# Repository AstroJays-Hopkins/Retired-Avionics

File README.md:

# Onboard Avionics and Ground Support Electronics

Avionics computer programs (excluding ground station GUI) and circuit schematics.  Program design documents and other non-program files may be found on team internet storage.

## Some directories of interest

* ```propulsion/```  --- Programs that control rocket propulsion systems
  * ```propulsion/darts```  --- Rocket's Data Acquisition, Recording, and Telemetry System
  * ```propulsion/ignition```  --- Programs to monitor and actuate the rocket's ignition hardware
* ```recovery/```  --- Programs that make sure the rocket can fly again
* ```ground-tests/```  --- Programs to help determine if the rocket can (should) even fly in the first place
* ```libraries/```  --- Custom libraries written in-house (one-of-a-kind --- you won't find them elsewhere!) and modified sensor libraries.

For detailed information about a particular subsystem, please consult the READMEs in that subsystem's directory.

_Made in Baltimore with love, tears, caffine, swearing, all-nighters, hair-pulling, stolen code, grimacing, git-cursing, and shocking realizations about engineering._

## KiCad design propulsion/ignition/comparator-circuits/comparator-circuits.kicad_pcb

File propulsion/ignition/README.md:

# Ignition system programs and schematics

Name says it all.

Schematic and PCB design are done using [KiCAD](http://kicad-pcb.org/).

## Files

* ```schematic/```  --- Schematics for ignition system
* ```comparator-circuits/```  --- Schematics and PCB design files for the
  continuity tester circuits used in the ignition system

### Things to know about the schematics

* Suggested changes to the schematics are presented in the ```future``` branch.

## Explanation of system

> _Bug avnoks for further details._

The ignition system consists of three parts: the part to light the ematch,
the part to open the oxidizer ball valve,
and the radio device (the "football") that controls the first two parts.
The system is designed around the following principles:

* Safety is implemented in hardware.
  The system's safety should arise from its physical properties,
  not from software checks.
  > Use physical switches as opposed to if statements.
  Never should software be the only thing preventing an unauthorised launch.
* The system should fail safe.
  Should a component of the system stop working,
  it should do so in a way that does not compromise the rest of the system
  and does not cause an unauthorised launch.
* Ultimate control of the system and the launch of the rocket
  should reside in one person.
  This is accomplished by giving the one key
  that arms all switches throughout the system and launches the rocket
  to only one person who is also the last person to leave the pad.
* The system should communicate unambiguously.

### Ematch

The ematch part of the system consists of a battery,
an ematch,
and circuitry to prevent the battery from lighting the ematch
when it's not supposed to.
The battery is housed alongside a relay, radio, and other circuitry
in a relay box located 50 imperial feet away from the rocket
(the radio recieves the command to light the ematch
and activates the relay to connect the battery
to the wires going to the ematch).
The ematch is buried in a block of propellant
suspended in the fuel grain of the rocket;
it is connected to the relay box
through a long wire and some more safety circuitry.
The safety circuitry consists primarily of voltage warning signals,
two switches,
and continuity testers

#### Voltage warning signals

A buzzer and a white LED
in the relay box
and another buzzer and white LED in the rocket
warn launch personnel when there is voltage across the wire
that supplies the ematch with electricity.
Should launch personnel observe these buzzers and LEDs activate,
they should immediately retreat from the pad
and await further instructions.

**FIXME:** Identify frequency of buzzer.

#### Switches

Two key switches are built into the circuit:
a shunt switch,
which is on the relay box,
and a safety switch,
which is on the rocket.
The shunt switch shorts out the wires
that supply electricity to the ematch.
It should be closed whenever personnel are closer to the rocket
than the relay box is (within 50 feet of the rocket).
The safety switch interrupts the wires supplying electricity to the ematch.
It should remain open unless personnel
are about to retreat to a safe area for launch.
Personnel should never close the safety switch
if they observe the voltage warning signals described above.

#### Continuity testers

The continuity testers detect when the switches,
relay,
and ematch in the system have continuity.
For the relay and switches,
the testers sound a buzzer and light an LED
when the component monitored is in an unsafe state
(unsafe means that fewer things need to happen
in order for the rocket to launch).

The continuity testers are built from comparators.
The theory behind them can be found at David Johnson-Davies's
[post on a similar tester.](http://www.technoblogy.com/show?1YON)
In short,
one of the comparator's inputs is tied to a voltage reference
created using a voltage divider.
The other input is connected to one side of the device
whose continuity is to be tested;
the ground of the comparator
is connected to the other side.
When there is continuity,
the second input of the comparator is shorted to ground,
which is less than the reference voltage.
This activates the comparator's output,
which turns on various buzzers and LEDs.

The LM393 comparators used in the system
is an open collector device ---
its output conducts to ground when it is active.

### Motorised Ball Valve (MBV)

Radio module receives launch signal from football.
Waits a bit for relay box to light ematch
and start combustion of fuel grain.
Then checks to see if there still is continuity across the ematch.
If there isn't (match has burnt through),
opens ball valve.

**FIXME:** Where's all the code?

### Football

Radio transceiver that transmits launch command to MBV and relay box.
Should in future receive and display continuity tester data
back from relay box and rocket
(state of relay, switches, and ematch).

## Things to fix

- [ ] **TODO:** Teach everyone on the team what the different signals
                (voltage, continuity)
                look and sound like.
- [ ] **TODO:** Post labels on system describing what to do if a particular signal is observed.

- [ ] __TODO:__ Check design of system in ```future``` branch,
                then order new PCBs.
- [ ] __TODO:__ Assemble modified system

- [ ] __TODO:__ Label physical components with designators from schematics
- [ ] __TODO:__ Build physical housing for system

- [ ] __VERIFY:__ Does MBV controller know when ematch has burnt through?

- [ ] __FIXME:__ Optoisolate inputs between different parts of system
- [ ] __FIXME:__

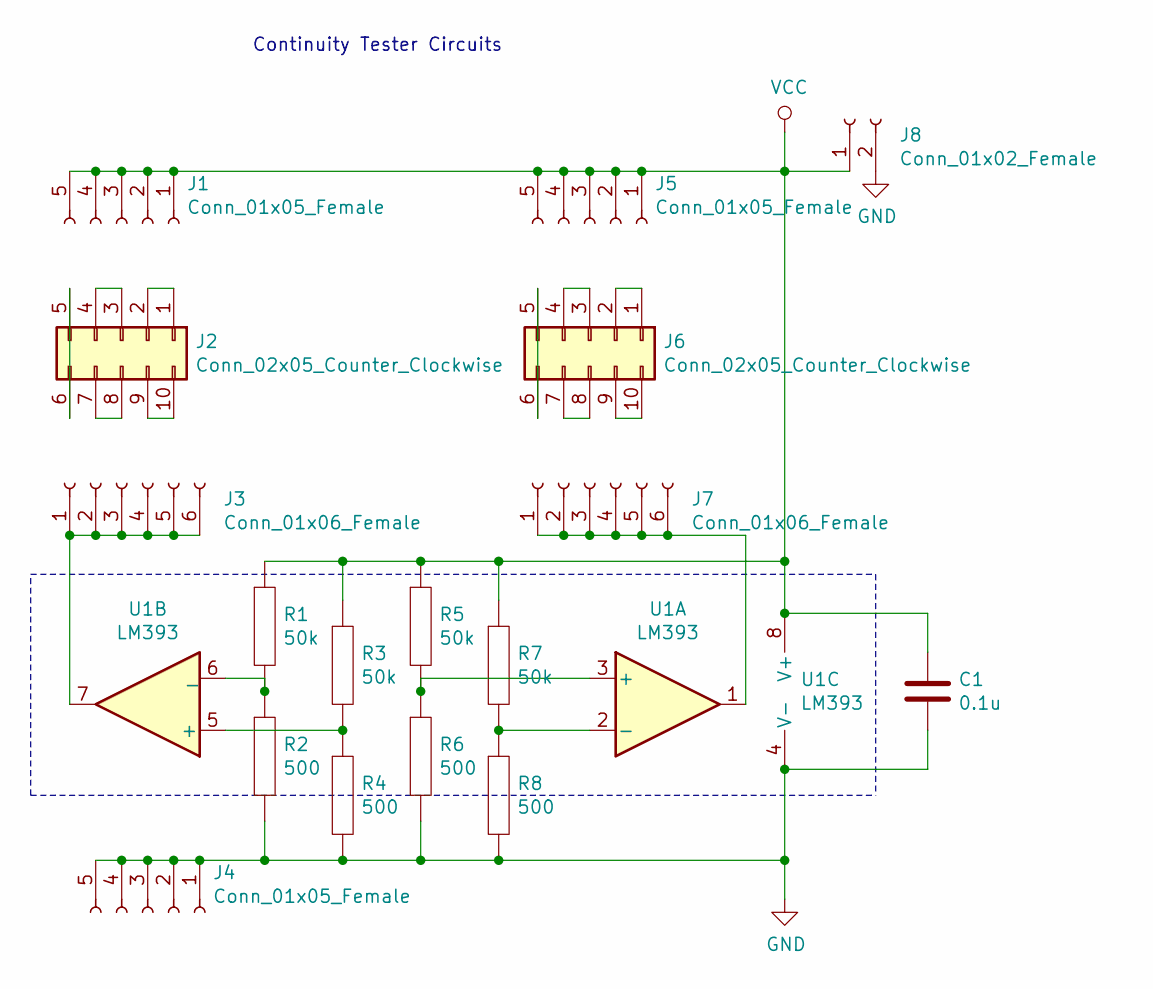
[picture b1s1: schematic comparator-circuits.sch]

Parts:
C1: 0.1u; C_Disc_D3.0mm_W2.0mm_P2.50mm
J1, J4, J5: Conn_01x05_Female; PinHeader_1x05_P2.54mm_Vertical
J2, J6: Conn_02x05_Counter_Clockwise; PinHeader_2x05_P2.54mm_Vertical
J3, J7: Conn_01x06_Female; PinHeader_1x06_P2.54mm_Vertical
J8: Conn_01x02_Female; PinHeader_1x02_P2.54mm_Vertical
R1, R3, R5, R7: 50k; R_Axial_DIN0207_L6.3mm_D2.5mm_P7.62mm_Horizontal
R2, R4, R6, R8: 500; R_Axial_DIN0207_L6.3mm_D2.5mm_P7.62mm_Horizontal
U1: LM393; DIP-8_W7.62mm

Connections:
GND: C1.2, J4.1, J4.2, J4.3, J4.4, J4.5, J8.2, R2.2, R4.2, R6.2, R8.2, U1.4 (V-)
unnamed: J2.1, J2.2
unnamed: J2.3, J2.4
unnamed: J2.5, J2.6
unnamed: J2.7, J2.8
unnamed: J2.9, J2.10
unnamed: J3.1, J3.2, J3.3, J3.4, J3.5, J3.6, U1.7
unnamed: J6.1, J6.2
unnamed: J6.3, J6.4
unnamed: J6.5, J6.6
unnamed: J6.7, J6.8
unnamed: J6.9, J6.10
unnamed: J7.1, J7.2, J7.3, J7.4, J7.5, J7.6, U1.1
unnamed: R1.2, R2.1, U1.6 (_)
unnamed: R3.2, R4.1, U1.5 (+)
unnamed: R5.2, R6.1, U1.3 (+)
unnamed: R7.2, R8.1, U1.2 (-)
VCC: C1.1, J1.1, J1.2, J1.3, J1.4, J1.5, J5.1, J5.2, J5.3, J5.4, J5.5, J8.1, R1.1, R3.1, R5.1, R7.1, U1.8 (V+)

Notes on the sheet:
Continuity Tester Circuits

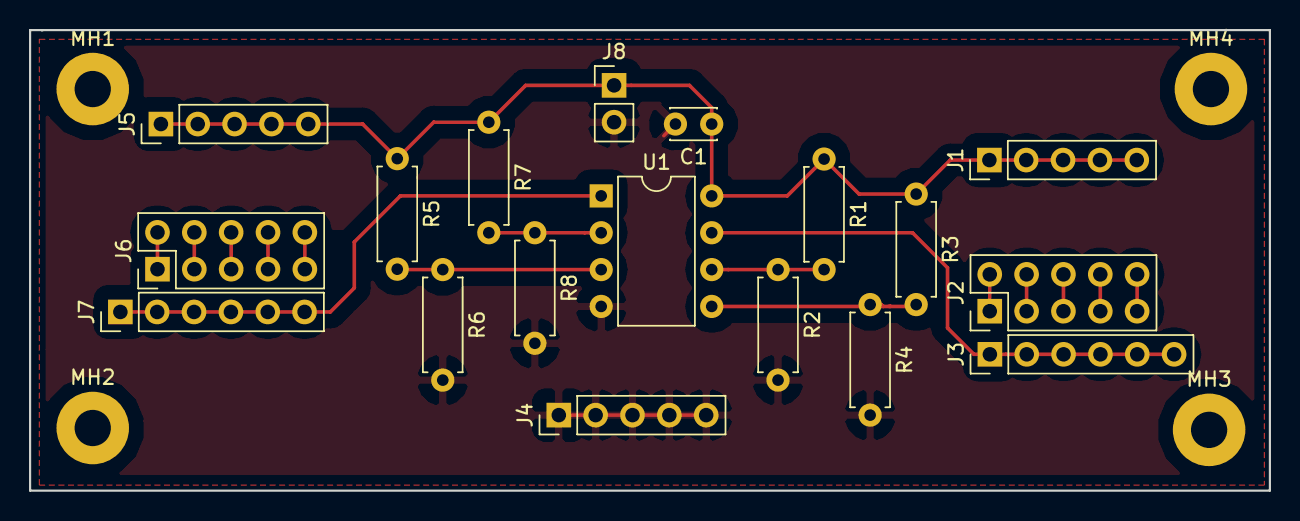
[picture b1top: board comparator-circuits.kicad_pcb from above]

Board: 2 copper layers, 85.5 x 31.8 mm, 22 parts (0 on the bottom side), 18 nets.

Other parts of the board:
MH1, MH2, MH3, MH4: MountingHole_2.5mm_Pad

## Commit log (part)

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2018-03-04 Create Libraries
2018-03-04 Rename Libraries to README
2018-03-11 Add files via upload
    Operational code, not including RF communication
2018-11-02 Update 1
    Added datalogging capability for all variables, not just average altitude
2018-11-16 latest working code
2018-11-16 Added music library.
2018-11-16 [Removed backup file]
2018-11-30 Update Hybrid.ino
    Created an array of thermocouples to take temperature values at two points on the run tank and combustion chamber
2018-11-30 Update Hybrid.ino
    Resized thermocouple temperature arrays
2018-12-04 Update Hybrid.ino
    Updated thermocouple sensor/data array structures, redefined value for ignition command, nested ignition command in conditional statement that tests for arming condition so ignition cannot occur duri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
2018-12-23 Added range test code. Fixed indentation of bracket in Hybrid.ino .
2019-01-11 Radio identity now determined by shorting out input pin. Added function calls to print debug information; increased number and length of delays.
2019-01-13 Update MEGA.ino
    Added rocket stage logging/monitoring to SD,RF capabilities
2019-01-13 State-unique songs
    Added armed, thrust, descent, and recovery sounds
2019-01-31 Record-keeping ... updated range test code that we won't use.
2019-02-02 First Contact
    -changed radio communication libraries
    -restructured RF communication to only send flight data to ground station
2019-02-03 Wet Dress v0.9.1
    Added 915 MHz LoRa communication instead of 2.4 GHz
    Takes input from load cells
2019-02-25 Update Wet Dress.ino
    added venting timer
2019-03-01 Update GROUND_STATION.ino
    added new LoRa library, parses single packet for info rather than logging individual values sent, adds datalogging capability
2019-03-02 Added program to test ball valve motor.
2019-03-02 Fixed relay pin constant in turn_motor_on_reverse(); edited comment.
2019-03-03 Rename Sensing_Mega.ino to Cold Flow/Sensing_Mega.ino
2019-03-03 Rename Ground_Station_Reader.ino.ino to Cold Flow/Ground_Station_Reader.ino.ino
2019-03-03 Program Functionality
2019-03-03 Update Ground_Station_Reader.ino
    Added datalogging capabilities
2019-03-07 Moved sketch files to individual directories.
2019-03-07 Added button press detection/timing, SD logging
2019-03-17 Created "propulsion" directory; added initial load cell functions and main.py
2019-03-18 test file
2019-03-18 Revert "folder change"
    This reverts commit 8c865882d8dbeeaf4b2815698954fac62de97615.
2019-03-18 More directory reorganization. Created "ground-tests", "recovery" directories. Moved several relevant files and directories to new directories.
2019-03-24 Networking using socket.py with Pi as the server
2019-03-24 Rename client.py to Client.py
2019-03-24 Moved "Client.py", "RocketThermocouple.py", "Server.py", and "socket.py" to "propulsion/". Modified MUX select functions for load cells and load-cell read-iteration; added torpedo's logging routines 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
2019-03-24 added documentation
2019-03-24 Subclassed MAX31855 thermocouple class.
2019-03-24 note to change critical checks to 2 state system
2019-03-24 added import RocketThermocouple
2019-03-30 added to do list and assigned functions
    :)
2019-03-30 Added code to read PTs, init PTs and TCs; modified main.py .
2019-03-31 replaced get_state functions; defined state variables
2019-04-02 Select Tuple pinouts update
    16, 18 chosen for WDR/CFT
2019-04-02 Variable pins
    Added pinouts for previously u
2019-04-02 RF transmission of ball valve commands
2019-04-03 Switched to BCM GPIO #s
    BCM boissss
2019-04-03 Bugfixes. Nuff said.
2019-04-04 Some quick changes that I no longer remember...
2019-04-05 Bugfixes and feature additions galore. Now communicates over WiFi. Lots of other things done.
2019-04-20 Implemented RF control of vent and DC solenoids
2019-04-26 for use with RFHybridController.ino
2019-04-26 added ignition setup
2019-04-26 fuelRelay, clear rfInput
2019-04-27 Changed index of command string used to for ignition character in Ball_Valve.ino; added program for relay box.
2019-05-02 set controller-side ignition safety, ignition state as BV variable
2019-05-05 Arduino program to read load cells/relay to pi
2019-05-12 Courtney made some edits
2019-05-12 yeehaw
2019-05-12 Add changes on main.py --> Update number of PTs, TCs, and load cells.
2019-05-15 added safety counter variable to prevent repeat ignition
2019-05-15 Fixed bug that read char as ASCII values
2019-05-15 Updated files and moved to individual directories.
2019-08-18 Modified continuity tester circuits for relay box, changed D6 to schottky diode, removed one relay for ball valve motor control.
2019-09-07 Cleaned code in main.py rocket_thermocouple.py load_cell.py
2019-09-08 More changes, bugfixes.
2019-10-05 darts: Misc changes
    Modified TC callibration and general error messages in data
    collection failures.
2019-10-06 darts: LC_Reader convert to new format
    Convert loadcells class to read loadcells using the new openscale firmware.
    The new firmware has been configured to output a string in the format
    `[timestamp],[value],[units],` every 100ms. Since our current loop
    interval is configured to cycle every 0.01s, we return the last buffered
    read until the loadcell has new data available. Read logic has been
    moved from a free standing function to a class to enhance code
2019-10-06 load_cell.py Docstring improvements
    Fixed typoes and added docstrings for the two loadcell classes.
2019-10-06 load_cells.py: Fix disconnected loadcell state
    Incorrect exception handler, it should set the loadcell list to none to
    allow the logic test. This is kludge and should be removed when it's
    time to go to prod.
2019-10-06 Add files via upload
    This is the Arduino code used as transmitter for testing of the valve control of inboard Arduino, imitates the behaviour of football.
2019-10-12 darts/load_cell.py: Fix typo
    Small typo causing syntax errors is now fixed. CI could have prevented
    this from being committed.
2019-10-12 darts/load_cell.py: Tweak read params
    Read, then dump buffers when data is available to prevent waiting for
    new data and blocking the entire read loop.
2019-10-13 Add relay_box_pintest.ino
    This is the Arduino code used as transmitter for testing of the valve control of inboard Arduino, imitates the behaviour of football.
2019-10-14 darts/main.py: Separate out constants
    Move constants out of the global namespace into their own class. Keeping
    namespace clean is always a good idea.
2019-10-14 darts/main: Add DACCLoop Class
    All data collection and command and control has now been moved into a
    class. This is part five of the refactor and concludes the major
    changes.
2019-10-14 darts/pressure_transducer: Use Reader Class
    Converted the scattered reading functions to a reader class to allow
    easier PressureTransducer object manipulation.
2019-10-15 Update IntegratedValveControl.ino
    Replaced the interrupt with a timer control, whilst making the code slightly more compact.
2019-10-24 Update IntegratedValveControl.ino
    The updated code, partially finished, should be in compliant with the most recent spec for RF communications, and it should also work with ACK. Debugging is direly needed
2019-10-26 RFHybridController: Redo Buttons
    Fixes reliability issue with button by "debouncing" inputs for 50ms
    before allowing accepting the input. This prevents button activation
    occilations from effecting the output and causing multiple commands to be
    sent.
    Buttons have been modularized into a struct. While this is cpp, care has
    been taken to minimize performance and cruft overhead of running cpp on
2019-10-26 RFHybridController: Formatting Fixes
    Standardized indent to four spaces, one space between if condition and
    opening brace, and linewrap at 80 chars.
2019-10-26 RFHybridController: Update to latest Spec
    Updated ground station frimware to be compliant with v0.4.0 of the
    Propulsion Avionics Control Plane Spec. This includes new acking
    protocols, a more logical command scheme (0 is now always a noop),
    formalization of packet headers/metadata, and a sequence code based
    command synchonization. NACKs are pending in a future revision of the
    specs.
2019-10-26 ValveControl: Fix control scheme
    Fixed the acks to properly correspond with sequence.
2019-10-28 ValveControl: Split out common constants
    Split constants header to shared constant and device specific constant headers
    to enhance reusability and readability.
2019-10-28 VavleControl: Fix Radio heartbeats
    Hearts beats were not being processed correctly. They should work
    properly now.
2019-10-28 StepperController: Add initial implementation
    Implemented the stepper controller to control the ground-side fueling
    valve. Currently, it relies on the I2C bus master to update its status
    as necessary.
2019-10-28 darts: Implement I2C Engine Interface
    Using I2C simplifies wiring and enhances reliability, while allowing more
    data to be sent as necessary. Overall, this is a much more robust system
    that should fail less and more predictably
2019-10-31 RFHybridControler: Move pins to const
    Moved pin names to constant file, and fixed pins to not conflict with
    radio communications. Also fixed small logic errors preventing the
    controller from working properly.
2019-10-31 StepperController: Fix Turn logic
    Missing breaks in switch statement cuased open comands to carry on to
    close commands, thereby actuating a net 0 rotation. this is now fixed
    and the actuation should proceeded as expected. Also, lockouts have been
    added to prevent the valve from actuating in the same direction twice.
2019-10-31 RFHybridController: Add Solenoid Lockout
    Lockout solenoid in closed (flow open) position until the rocker switch
    is flipped to the on position, which will then allows the button to be
    used to manually trigger vent.
2019-10-31 RFHybridController: Enable Ignition
    Enabled ignition comamnd for testing purposes.
2019-11-02 StepperController: Disable movement on first read
    Prevented the stepper controller from moving at the first read and
    synced the flight computer state to prevent movement in the wrong
    direction if the valve is not in the initial position expected.
2019-11-04 IVC: Use encoder for motor control
    Since the encoder ouputs 4 pulses on each channel per revolution (or
    seven total for one revolution cosering both and having b offset from 8
    by 90deg), we've found the max pulse rate to be 700hz. This is more than
    10ms to react to each pulse, so we've put pulse counting into an
    interrupt. Preliminary analysis suggests that the speed impact of this
    isn't too bad...
2019-11-06 Valve Control: Fix valve state conventions
    OPEN means that the valve allows flow and CLOSED means that the valve
    does not allow flow. Remember this you doofus! In other words, the vent
    valve now folows sane human valve conventions.
2019-11-12 ValveControl: Adjust MV-R1 movement offsets
    Dialed in new offset for the new valve. Backlash isn't consistent under
    pressure, but this is the closest we've been able to get full open using
    the encoder on the motor end.
2019-11-20 ValveControl: Add auto run stop after ignition
    Due to burn-through worries, we will shut the run down seven seconds
    after the ignition valve is opened. this will prevent ox flow and the
    control panel operator shall manually actuate it open after flame out is
    confirmed to finish venting.
2019-11-20 engine_controller.py: Optimize initialization
    Variable is initialized to proper value on the first statement, instead
    of using another superfluous statement.
2020-02-21 darts: Archive old files
    Moved all defunct code out to prepare for deletion.
2020-02-22 darts: Organize into modules
    Moved python files so that it follows proper submodule organization to
    aid the transition to threaded code.
2020-02-22 darts: Add requirements.txt
    Added python pip dependencies.
2020-03-08 completed code of the library for load cell. Now needs testing
2020-03-12 snapshot 1
2022-04-08 added wiring info, corrected typos, added all libraries to folder
2022-04-10 Fixed compilation issues...
    ...by committing major software sins. :(
